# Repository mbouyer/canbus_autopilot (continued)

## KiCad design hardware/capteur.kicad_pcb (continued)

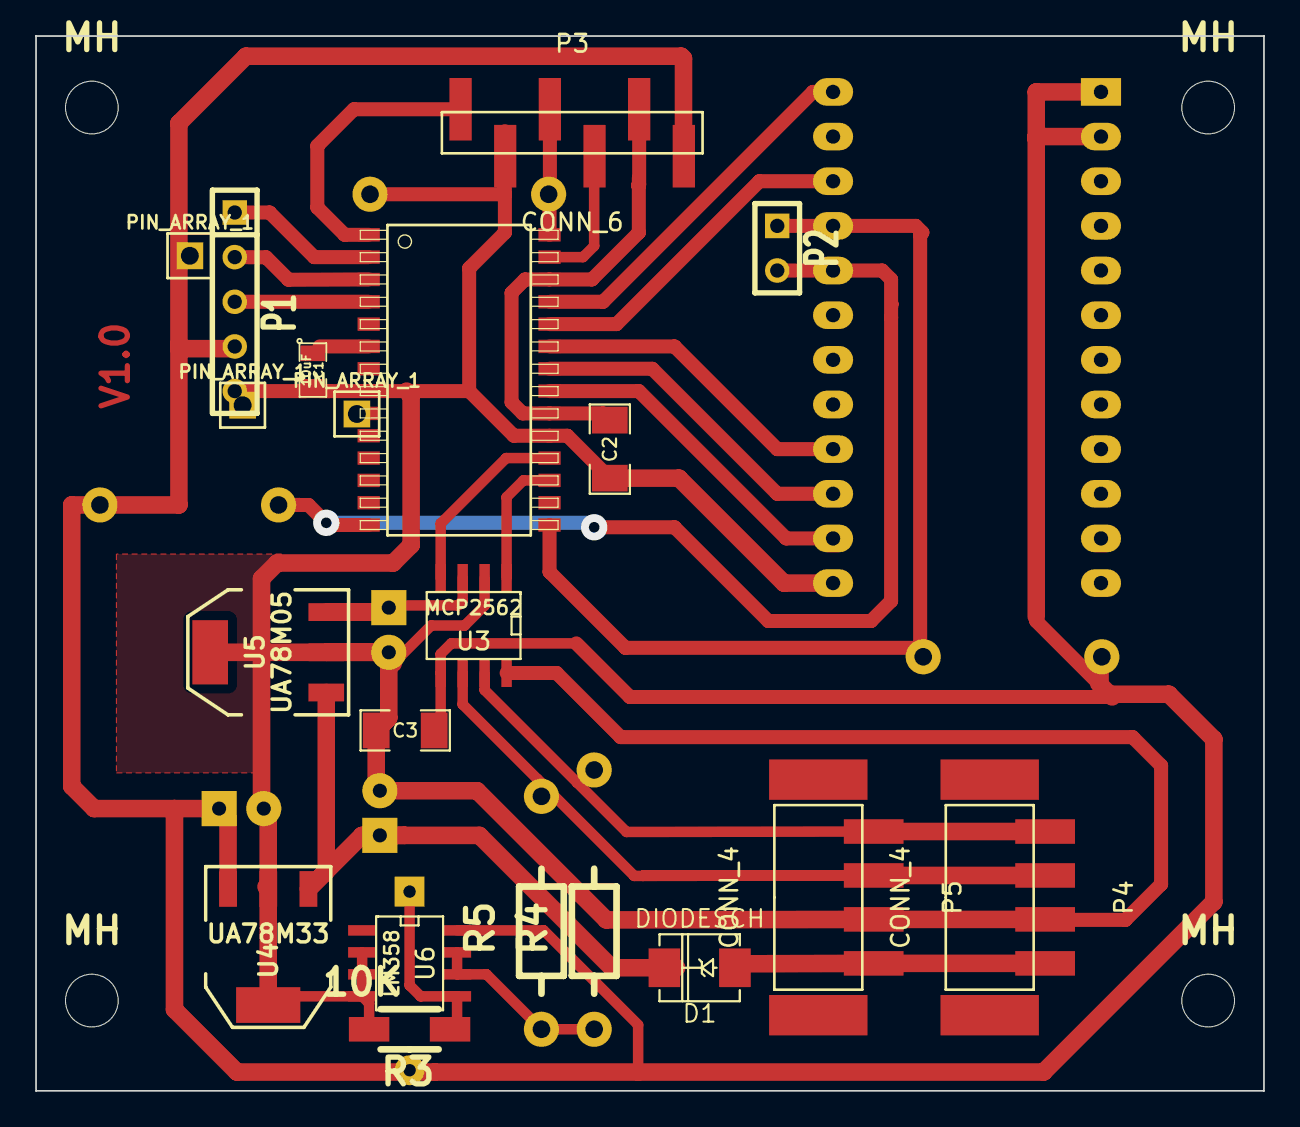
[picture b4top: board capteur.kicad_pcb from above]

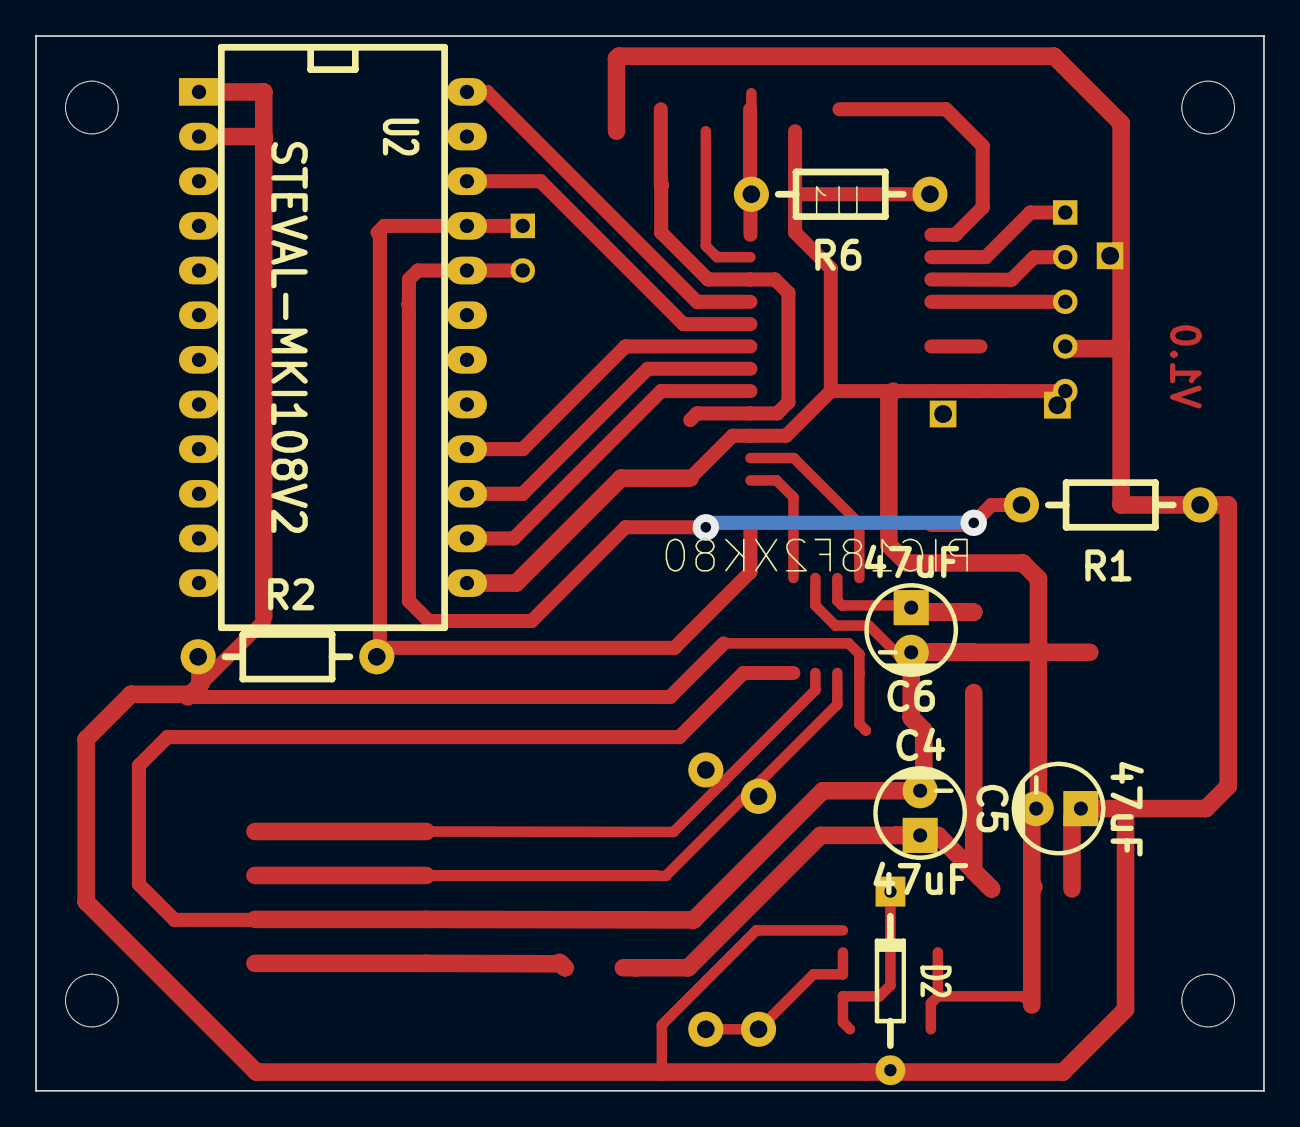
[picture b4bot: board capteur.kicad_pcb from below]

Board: 2 copper layers, 69.8 x 60.0 mm, 32 parts (8 on the bottom side), 26 nets.

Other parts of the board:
MH: MountingHole_3mm_RevA_Date21Jun2010
MH#2, MH#3, MH#4: MountingHole_3mm_RevA_Date21Jun2010
PIN_ARRAY_1, PIN_ARRAY_1#2, PIN_ARRAY_1#3: Val**; PIN_ARRAY_1

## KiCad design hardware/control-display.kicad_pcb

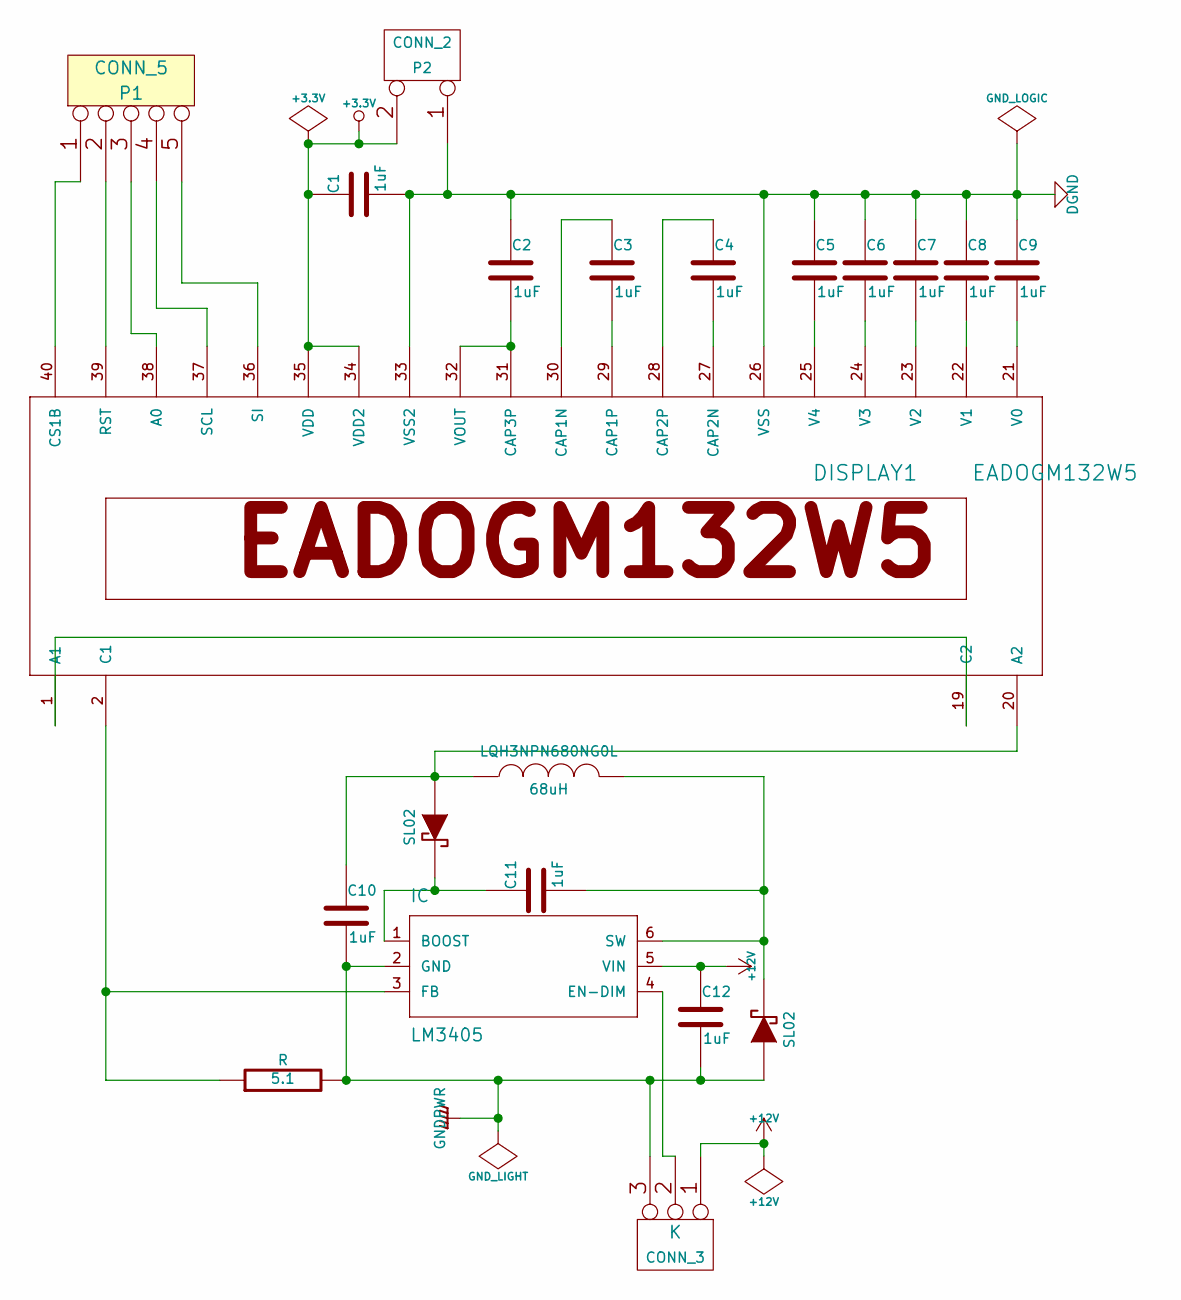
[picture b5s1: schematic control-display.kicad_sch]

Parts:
C1, C2, C3, C4, C5, C6, C7, C8, C9, C10, C11, C12: 1uF
D1, D2: SL02
DISPLAY1: EADOGM132W5
IC1: LM3405
K1: CONN_3
L1: 68uH
P1: CONN_5
P2: CONN_2
R1: 5.1

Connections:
+3.3V: C1.1, DISPLAY1.34 (VDD2), DISPLAY1.35 (VDD), P2.2 (PM)
+12V: C12.1, IC1.5 (VIN), K1.1
DGND: C1.2, C2.1, C5.1, C6.1, C7.1, C8.1, C9.1, DISPLAY1.26 (VSS), DISPLAY1.33 (VSS2), P2.1
GNDPWR: C10.2, C12.2, D2.1 (A), IC1.2 (GND), K1.3, R1.2
unnamed: C10.1, D1.1 (A), DISPLAY1.20 (A2), L1.1
unnamed: DISPLAY1.2 (C1), IC1.3 (FB), R1.1
unnamed: C11.1, D1.2 (K), IC1.1 (BOOST)
unnamed: C11.2, D2.2 (K), IC1.6 (SW), L1.2
unnamed: DISPLAY1.1 (A1), DISPLAY1.19 (C2)
unnamed: IC1.4 (EN-DIM), K1.2 (PM)
unnamed: DISPLAY1.39 (RST), P1.2
unnamed: DISPLAY1.36 (SI), P1.5
unnamed: DISPLAY1.40 (CS1B), P1.1
unnamed: DISPLAY1.38 (A0), P1.3
unnamed: DISPLAY1.37 (SCL), P1.4
unnamed: C9.2, DISPLAY1.21 (V0)
unnamed: C8.2, DISPLAY1.22 (V1)
unnamed: C7.2, DISPLAY1.23 (V2)
unnamed: C6.2, DISPLAY1.24 (V3)
unnamed: C5.2, DISPLAY1.25 (V4)
unnamed: C3.1, DISPLAY1.30 (CAP1N)
unnamed: C2.2, DISPLAY1.31 (CAP3P), DISPLAY1.32 (VOUT)
unnamed: C4.2, DISPLAY1.27 (CAP2N)
unnamed: C4.1, DISPLAY1.28 (CAP2P)
unnamed: C3.2, DISPLAY1.29 (CAP1P)

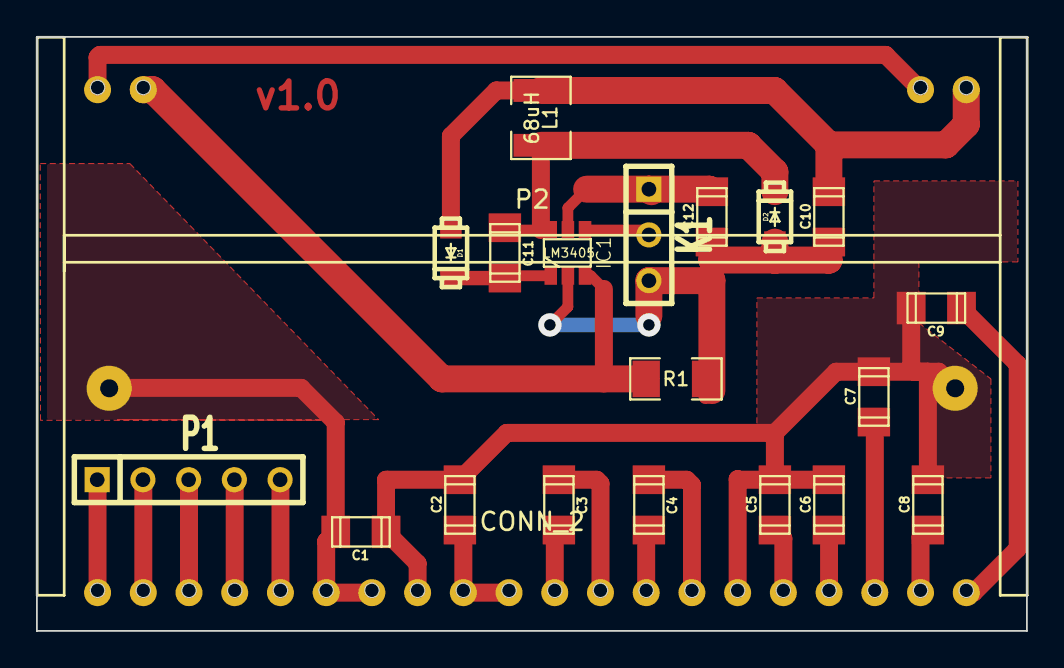
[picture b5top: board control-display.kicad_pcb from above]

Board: 2 copper layers, 55.0 x 33.0 mm, 21 parts (1 on the bottom side), 25 nets.

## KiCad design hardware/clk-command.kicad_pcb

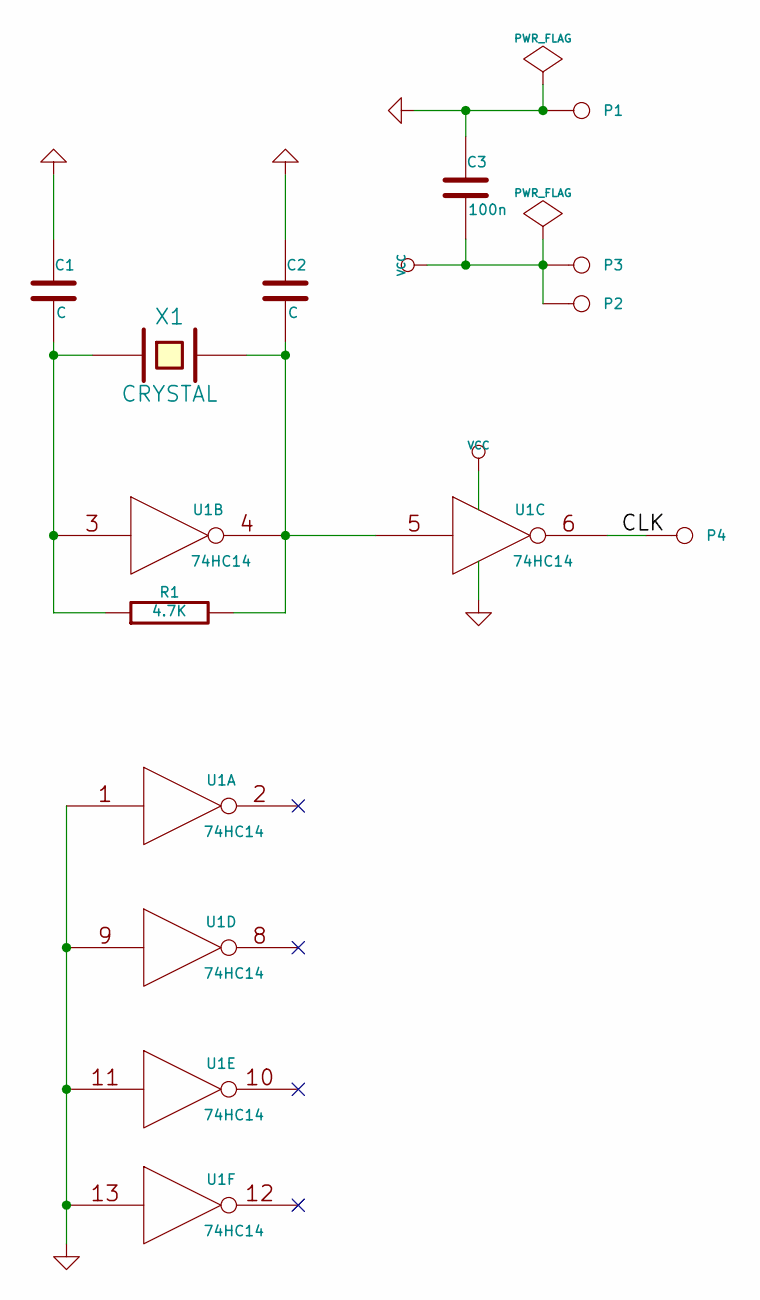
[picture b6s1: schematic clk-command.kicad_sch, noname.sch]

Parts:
C1, C2: C
C3: 100n
P1, P2, P3, P4: CONN_1
R1: 4.7K
U1: 74HC14
X1: CRYSTAL

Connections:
/CLK: P4.1, U1.6
GND: C1.1, C2.1, C3.1, P1.1, U1.1, U1.7 (GND), U1.9, U1.11, U1.13
unnamed: C2.2, R1.2, U1.4, U1.5, X1.2
unnamed: C1.2, R1.1, U1.3, X1.1
VCC: C3.2, P2.1, P3.1, U1.14 (VCC)

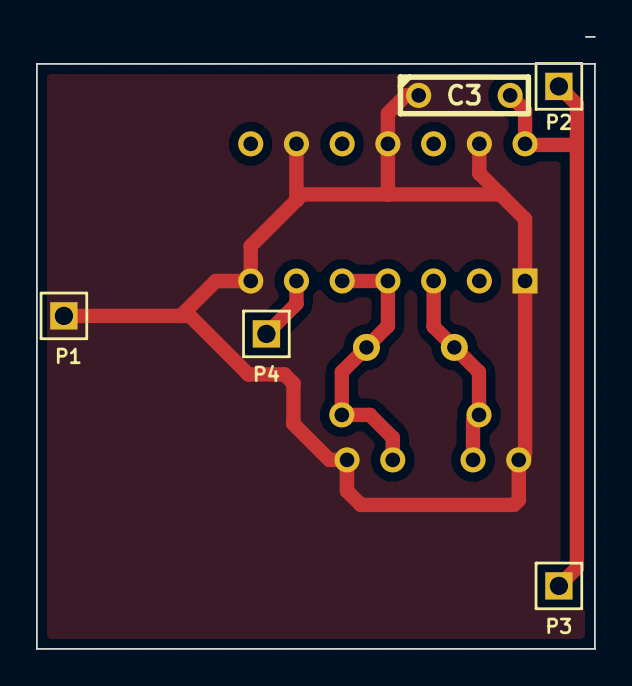
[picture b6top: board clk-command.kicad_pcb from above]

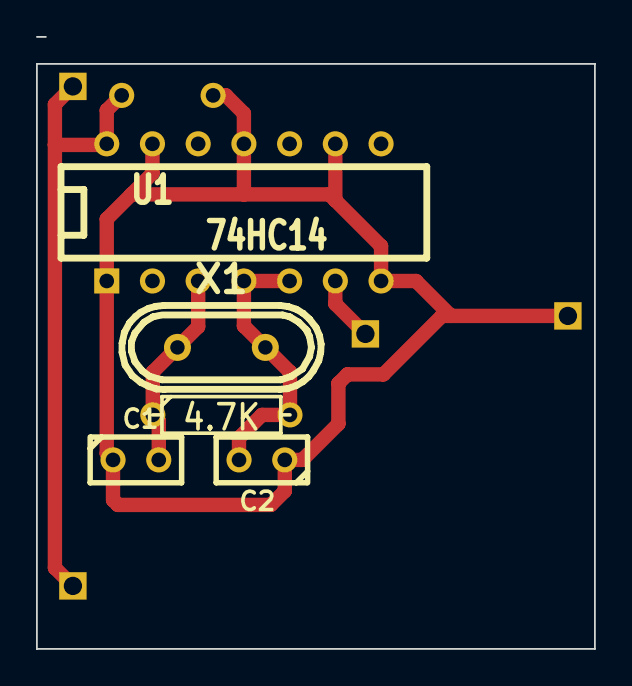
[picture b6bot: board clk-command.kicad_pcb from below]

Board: 2 copper layers, 31.0 x 34.0 mm, 10 parts (5 on the bottom side), 5 nets.

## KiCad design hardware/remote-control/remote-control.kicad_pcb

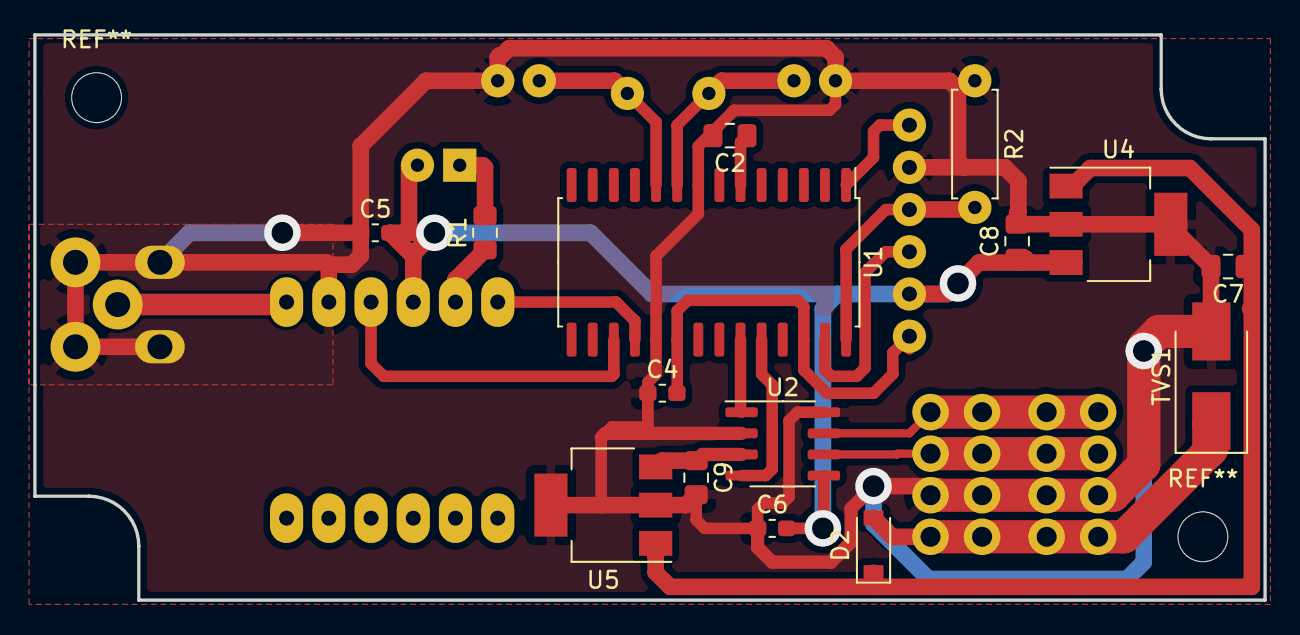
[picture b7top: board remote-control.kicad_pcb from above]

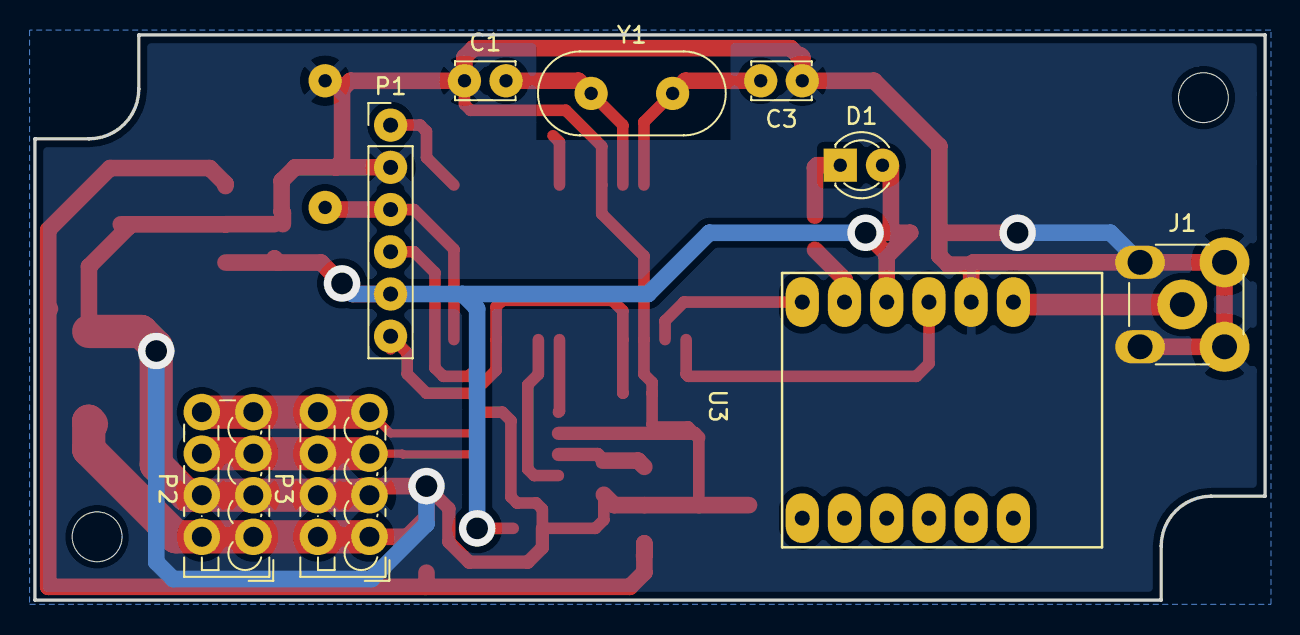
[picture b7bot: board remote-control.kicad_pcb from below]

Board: 2 copper layers, 74.0 x 34.0 mm, 24 parts (9 on the bottom side), 21 nets.

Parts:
C1, C3: 22pF; C_Disc_D3.4mm_W2.1mm_P2.50mm
C2, C7, C8, C9: 10uF; C_0805_2012Metric_Pad1.15x1.40mm_HandSolder
C4, C5, C6: 100nF; C_0603_1608Metric_Pad1.05x0.95mm_HandSolder
D1: LED; LED_D3.0mm
D2: PMEG4005EGWX; D_SOD-123
J1: Conn_Coaxial; SMA_Molex_73251-2200_Horizontal
P1: CONN_6; PinHeader_1x06_P2.54mm_Vertical
P2, P3: CONN_4; TerminalBlock_Phoenix_PTSM-0,5-4-2.5-V-THR_1x04_P2.50mm_Ver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
R1: 330; R_0805_2012Metric_Pad1.15x1.40mm_HandSolder
R2: 10K; R_Axial_DIN0207_L6.3mm_D2.5mm_P7.62mm_Horizontal
TVS1: SMBJ16A; D_SMB_Handsoldering
U1: PIC18F2XK80; SOIC-28W_7.5x17.9mm_P1.27mm
U2: MCP2562; SOIC-8_3.9x4.9mm_P1.27mm
U3: ZPT; RFsolutions_ZPT-D
U4: UA78M33; SOT-223-3_TabPin2
U5: UA78M05; SOT-223-3_TabPin2
Y1: 10Mhz; Crystal_HC18-U_Vertical

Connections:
+3.3V: C5.2, C6.2, C8.1, D1.2, P1.5, U2.5, U3.4, U4.3
+5V: C9.1, U2.3, U5.3
+12V: C7.1, D2.1, U4.1, U5.1
/12Vin: D2.2, P2.1, P3.1, TVS1.1
/ANT: J1.1, U3.1
/CANN: P2.3, P3.3, U2.6
/CANP: P2.4, P3.4, U2.7
/CANRX: U1.24, U2.4
/CANTX: U1.23, U2.1
/PGC: P1.4, U1.27
/PGD: P1.3, R2.2, U1.28
/~MCLR: P1.1, U1.1
GND: C1.1, C2.2, C3.1, C4.1, C5.1, C6.1, C7.2, C8.2, C9.2, J1.2, P1.2, P2.2, P3.2, R2.1, TVS1.2, U1.8, U1.19, U2.2, U2.8, U3.2, U4.2, U5.2
unnamed: C1.2, U1.9, Y1.1
unnamed: C2.1, U1.6
unnamed: C3.2, U1.10, Y1.2
unnamed: C4.2, P1.6, U1.20, U1.26
unnamed: D1.1, R1.2
unnamed: R1.1, U3.5
unnamed: U1.17, U3.3
unnamed: U1.18, U3.6

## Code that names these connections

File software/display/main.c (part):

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
#define SPKR_PORT	LATAbits.LATA3

#define ROTARY_A	PORTBbits.RB3
#define ROTARY_B	PORTBbits.RB2

#define SW1		(!PORTBbits.RB5)
#define SW2		(!PORTBbits.RB4)
#define SW3		(!PORTBbits.RB0)
#define SW4		(!PORTBbits.RB1)

/* beep freq: 19.53125Khz / x */
#define SPKR_440	44 /* 440Hz */
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
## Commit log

2019-03-13 Move autopilot software from CVS to github
2019-03-13 Initial move of the autopilot electronic design to github
2019-03-13 Add 2-close BSD license
2019-03-14 Remove commented out code
2019-03-14 Better clean target
2019-03-14 As we compute relative rudder moves, which accumulate over time, we can consider the PID as being against the rate of turn instead of heading. The target of the PID is a ROT of 0, with the heading er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
2019-03-15 Better names in the display page
2019-03-15 Use defines instead of hard-coded numbers for param slots
2019-03-15 Add labels to factors, and improve layout
2019-03-15 Better handling of timeouts
2019-03-15 Don't forget to update previous_rot_rate if you want to properly compute accelleration
2019-03-16 Account for the target change in the rate of turn, for faster reaction on target change
2019-03-17 Add a MUTE control message, which ask a device to stop sending user frames (only bus control is still handled). Add a socketcan tool to mute/unmute an address.
2019-03-17 Switch to use static reserved memory, avoids saving registers and multiple banksel. Saves about 15ms per round, or more than 16%.
2019-03-17 Move several variables from int to short; as sizeof(int) moved from 2 to 4.
2019-03-24 move timer0_read() from int to short, as now int == long handle rotary_pos in an interrupt_safe way Change timer2 from 1Khz to 500hz, for the benefit of PWM (one more bit) and key debounce Introduce 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
2019-03-24 Remove delay() in page_light(), it doesn't seem to help with the display bug. Fix light value sent. Correct timer2 frequency in comment.
2019-03-24 More use of get_rotary_pos(). Really use only 4 bits for rotary debounce.
2019-04-26 Add load/save pilot params
2019-05-01 Don't forget to initialize target_rudder
2019-07-29 Add schematic for the remote control receiver; based on RF solution ZPT-8RS receiver (transmitter is a fobber 8T8).
2019-07-29 Add firmware for remote control. Also introduce new PRIVATE_REMOTE_CONTROL messages transmitting informations about the remote controller.
2019-07-29 Factor out code switching the autopilot to standby. This makes sure that command_target_heading is always initialized.
2019-07-29 Display status of remote control
2019-07-29 Add small program listening for MOB messages on the can bus. It will call the script specified on command line.
2019-07-29 Use proper size for BEEP
2019-07-29 Add helper software listening for BEEP can messages and playing appropriate sound.
2019-08-03 NULL-terminate exec argument list
2020-02-13 use a more widely available font
2020-03-12 Add diplay cover design
2020-03-12 Add reverse display light status
2020-03-13 Adujst height of strait part to reality
2020-03-13 Adjust sizes after first print
2020-03-28 Binary starts at 1k
2020-03-28 Accept pilot mode change from main unit (we now allow multiple control/display unit)
2020-03-28 factor out backlight handling allow inverted (white on black) display
2020-03-28 Better contrast for reverse display Handle reverse in resetdisplay() too.
2020-04-05 If autopilot is on, allow to switch to standby from more pages - especially error pages.
2020-04-05 Add new REMOTE_DISPLAY control message
2020-04-05 Add a page allowing to send REMOTE_DISPLAY/REMOTE_DISPLAY_PAGE control messages
2020-04-13 CONTROL_REMOTE_DISPLAY_PAGE message: don't forget to set data len
2020-04-26 When a route is started or waypoint changes, switch to nav display (and beep)
2020-06-04 Try to dynamically detect rudder min/max limits. compile tested only.
2020-06-16 Fix offset so that we have a back wall.
2021-04-26 Move nmea2000 and radrandreg libraries to its own repository. Adjust paths.
2021-04-26 Consistency in FAKE support: name it FAKE everywhere comment it out everywhere remove it where it doens't make sense.
2021-04-27 After pic18_n2k update, define CAN_PORTB or CAN_PORTC, as appropriate
2022-01-28 Build .hex by default, we now use the can boot loader.
2022-01-29 Ajust for pic18_n2k changes
2022-07-21 Add a #define for motor overcurrent limit, and make it unsigned
2022-12-01 Convert to kicad 6.x
2023-06-26 move canhost_mute to pic18_n2k repo
2025-03-24 Design 3d-printed button for command's encoder
